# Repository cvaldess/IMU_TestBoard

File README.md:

# IMU Test Board

Four inertial sensors on one small, rigid PCB: **TDK ICM-45686**, **ST LSM6DSV320X**, **ST ASM330LHH** and
**ADI ADXL375**. Because they sit side by side on the same board, all four feel the same shocks, vibration and
temperature on a motocross bike, so their data can be compared directly.

The board is a test fixture for AI MotoLogger, a data logger for a motocross bike. The test results decide which IMU
goes on the main logger board.

*Concept illustration. The renders below show the actual board.*

| Bare board | Assembled board (3D render) |
|:---:|:---:|
|  |  |

## Sensors

| Ref | Part | Type | Accelerometer | Gyroscope | Package |
|---|---|---|---|---|---|
| U2 | TDK InvenSense ICM-45686 | 6-axis IMU | ±32 g | ±4000 dps | LGA-14, 2.5 × 3 mm |
| U3 | ST LSM6DSV320X | 6-axis IMU with a high-g channel | ±16 g, plus a ±320 g channel | ±4000 dps | LGA-14L, 2.5 × 3 mm |
| U4 | ST ASM330LHH | 6-axis IMU, automotive (AEC-Q100, −40 to +105 °C) | ±16 g | ±4000 dps | LGA-14L, 2.5 × 3 mm |
| U5 | ADI ADXL375 | 3-axis accelerometer | ±200 g | — | LGA-14, 3 × 5 mm |

The silkscreen numbers the chip selects and interrupts as `1 ICM · 2 DSV · 3 ASM · 4 ADXL`. The sensors are rotated
on the PCB so that their X, Y and Z axes match (U5 sits at −90° for this reason). The silkscreen marks the axes:
+X to the right, +Y up, and +Z out of the board (the silkscreen says *"+Z hacia fuera"*).

## What it is for

Each test answers one question.

On the bench:

1. Do all four sensors respond? Read `WHO_AM_I` / `DEVID`, and check that the ADXL375 is genuine (see the firmware notes).
2. How noisy is each sensor at rest compared with its datasheet (noise density, offset, drift with temperature)?
3. Do the high-g ranges agree? Under rubber-mallet hits, the ICM-45686 (±32 g) cross-checks the LSM6DSV320X high-g
   channel between 16 and 32 g, and the ADXL375 (±200 g) covers everything above.

On the bike:

4. How high are the real peaks? Do they go past 16 g, or past 32 g? Does any sensor saturate?
5. How does each sensor respond to engine vibration? Compare the spectra and the gyro drift under vibration (vibration rectification).
6. How hot does the board get? Read the internal temperature sensor of all four parts.
7. How accurate is the timing? Time-stamp each FIFO batch with its interrupt against the MCU counter.

The outcome is one of three choices for the main logger: the LSM6DSV320X alone, the ICM-45686 alone, or one of them
plus the ADXL375.

## Design

[`docs/IMU_TEST_BOARD.svg`](docs/IMU_TEST_BOARD.svg) is an English overview of the schematic. It also has the
firmware notes, the test plan, the wiring to the Nucleo and the layout rules. The notes in the KiCad schematic are in
Spanish.

- **Power:** 5 V comes in on J1, then goes through a 600 Ω ferrite bead (FB1) to a dedicated Torex XC6206 3.3 V LDO
  (U1). The IMUs do not share the MCU's 3.3 V rail. D1 is a power LED. The whole board draws less than 10 mA.
- **Shared SPI bus:** an SN74LVC1G32 OR gate sits in front of each IMU's SDI pin and outputs SDI = MOSI OR CS. While
  an IMU's CS is high, its SDI stays at 1, so traffic meant for another IMU can never look like an I²C start condition.
  The ADXL375 cannot turn off its I²C interface (datasheet Rev. B, Fig. 24), and the ICM-45686 datasheet does not say
  how to. RN1 pulls up every CS line, and R2 (33 Ω) sits in series with MISO.
- **ADXL375 supply:** R3 (0 Ω) links VS_ADXL to +3V3. If VS needs filtering, fit a ferrite bead in place of R3, not a
  resistor, because VS must stay ≥ VDD_IO.
- **Test points:** TP1 = +3V3, TP2 = GND, TP3 = ICM-45686 FSYNC (pin 9), for synchronisation tests later.

### J1 pinout and connection to a NUCLEO-U5A5ZJ-Q

J1 is a 1 × 15 header with 2.54 mm pitch. On the bench, it takes a male header and Dupont wires to the Nucleo. On the
bike, use a second board without the header: solder the cable into the J1 holes and tie it down through the two Ø3 mm
holes next to J1 for strain relief. Every signal goes through the Nucleo's Zio connectors, because the morpho headers
come unfitted.

| J1 | Silkscreen | Net | Nucleo | MCU pin | Function |
|---:|---|---|---|---|---|
| 1 | 5V | +5V_IN | CN8-9 | 5V | Nucleo 5 V output |
| 2, 4, 7 | GND | GND | CN8-11, CN7-8, CN8-13 | GND | |
| 3 | SCK | SCK | CN7-10 (D13) | PA5 | SPI1_SCK |
| 5 | MO | MOSI | CN7-14 (D11) | PA7 | SPI1_MOSI |
| 6 | MI | MISO | CN7-12 (D12) | PA6 | SPI1_MISO |
| 8 | CS1 | CS_ICM | CN7-16 (D10) | PD14 | GPIO |
| 9 | CS2 | CS_DSV | CN7-18 (D9) | PD15 | GPIO |
| 10 | CS3 | CS_ASM | CN7-20 (D8) | PF12 | GPIO |
| 11 | CS4 | CS_ADXL | CN10-2 (D7) | PF13 | GPIO |
| 12 | IN1 | INT_ICM | CN10-29 (D32) | PA0 | TIM2_CH1 |
| 13 | IN2 | INT_DSV | CN10-11 (A8) | PA1 | TIM2_CH2 |
| 14 | IN3 | INT_ASM | CN10-32 (D36) | PB10 | TIM2_CH3 |
| 15 | IN4 | INT_ADXL | CN10-34 (D35) | PB11 | TIM2_CH4 |

TIM2 is a 32-bit timer. Each interrupt line goes to one of its input-capture channels, so every FIFO batch gets a
timestamp without interrupt latency.

### Firmware notes

- Use SPI mode 3 for all four sensors (the ADXL375 requires it). The clock limits are 2–5 MHz for the ADXL375 (at
  least 2 MHz for 1600 and 3200 Hz output rates), 10 MHz for the ST parts and 24 MHz for the ICM-45686. At 5 MHz for
  all four, the data takes about 115 KB/s, or ~20 % of the bus.
- At start-up, disable I²C/I3C on U3 (`IF_CFG` 03h, `I2C_I3C_disable` = 1) and on U4 (`CTRL4_C` 13h,
  `I2C_disable` = 1), and turn off the internal pull-up on `AP_SDO` in U2 (ICM-45686 datasheet, Table 10).
- The ADXL375 reports the same `DEVID` (0xE5) as the ADXL345. At rest, a genuine ADXL375 reads 1 g as about 20 LSB
  (49 mg/LSB). A reading of about 256 LSB means the part is a relabelled ADXL345, a real risk with marketplace parts.

## PCB

| | |
|---|---|
| Size | 54.0 × 50.0 mm, rounded corners (r = 1 mm) |
| Layers | 4: top signals + GND pour / In1 GND plane / In2 +3V3 plane / bottom signals + GND pour |
| Thickness | 1.6 mm FR-4, 1 oz outer and 0.5 oz inner copper, no impedance control |
| Tracks | 0.20 mm signals, 0.40 mm power (0.15 mm minimum inside the IMU courtyards) |
| Clearance | 0.15 mm minimum (the LGA pads themselves are 0.15 mm apart) |
| Vias | 0.6 mm pad / 0.3 mm drill, tented |
| Holes | 4 × M3 (3.2 mm NPTH) for mounting, 2 × 3.0 mm NPTH for the cable tie |
| Finish | ENIG preferred: the 0.5 mm pitch LGA packages need flat pads |
| Parts | 32 SMD parts, all on the top side; J1 is through-hole |

The layout follows ST's TN0018 (handling, mounting and soldering of MEMS devices):

- No tracks, vias or copper pour under any IMU on the top layer, and pour keep-out areas under them on all four layers.
- The four IMUs sit in a row in the middle of the board, more than 8 mm from every mounting hole.
- J1 is more than 20 mm from the IMUs, because the cable pulls there. The LDO is more than 9 mm away, because it heats.
- The footprint pads are 0.1 mm larger than the LGA pads, and the solder mask opening is 0.1 mm larger than the pad.
- The paste apertures of U2–U5 are reduced by 0.025 mm per side, to 79 % of the pad area on the 2.5 × 3 mm parts and
  87 % on the ADXL375 (TN0018 §3.3 asks for 70–90 %).

## Fabrication files

| Folder | Contents |
|---|---|
| [`fabrication/pcbway/`](fabrication/pcbway) | The set sent to PCBWay: Gerber zip (RS-274X X2, Excellon drill with PTH and NPTH separate, job file), the same files unzipped plus PDF drill maps, a BOM with manufacturer part numbers, a centroid file, and [`README_PCBWay.txt`](fabrication/pcbway/README_PCBWay.txt) with the full spec and the MEMS handling notes. |
| [`fabrication/jlcpcb/`](fabrication/jlcpcb) | Gerber zip and unzipped files, a BOM with LCSC part numbers where they exist, and the KiCad pick-and-place file. These Gerbers were exported before the PCBWay logo was added. Only the top silkscreen differs; copper, mask, paste and drill are identical. |

The stencil is top side only, 0.12 mm stainless steel. The board is meant to be assembled by hand with the stencil.
When assembling:

- U5 (ADXL375) is rotated 270° on purpose, to align its axes with the other three sensors.
- J1 (1 × 15 header) is fitted by hand, and only on the bench board. TP1–TP3 are bare pads.
- Handle the MEMS parts as TN0018 says (the advice applies to the TDK and ADI parts too):
  - No ultrasonic cleaning.
  - No mechanical shocks: do not drop the parts or the boards.
  - Reflow to IPC/JEDEC J-STD-020, cooling no faster than 3 °C/s.
  - No solder on the sides of the LGA packages.
  - No underfill and no conformal coating.

## Opening the project

You need KiCad 10. Open [`kicad/prueba_imu.kicad_pro`](kicad/prueba_imu.kicad_pro) (*prueba_imu* is Spanish for
"IMU test").

- The symbols for the four IMUs are in [`kicad/libs/ai_motologger.kicad_sym`](kicad/libs/ai_motologger.kicad_sym),
  registered in the project's `sym-lib-table`.
- Footprints and 3D models come from the standard KiCad 10 libraries. The PCBWay logo is embedded in the board file.
- [`kicad/prueba_imu.kicad_dru`](kicad/prueba_imu.kicad_dru) adds three custom design rules (its comments are in
  Spanish):
  - `imu_pistas_finas` lets tracks narrow to 0.15–0.2 mm inside the IMU courtyards, so that power nets can reach the
    LGA pads.
  - `pasta_imu` applies the −0.025 mm solder paste margin on U2–U5. Only the absolute paste margin reaches the Gerber
    output; the relative margin does not.
  - `termico_un_radio` accepts a single thermal spoke on small SMD pads.

## Repository layout

```
kicad/          KiCad 10 project: schematic, PCB, custom DRC rules and the IMU symbol library
fabrication/    Gerber, drill, BOM and placement files (PCBWay and JLCPCB sets)
docs/           English schematic overview (SVG and PNG)
images/         Renders and the cover illustration
```

## Status

Rev 0.1. PCBWay sponsored the PCBs and the stencil (November 2026). The board has not been assembled or tested yet,
so treat the design as unverified. The next steps are hand assembly with the stencil, bench tests on a
NUCLEO-U5A5ZJ-Q, and then rides on a Yamaha YZ 125 test bike.

## Acknowledgements

Thanks to [PCBWay](https://www.pcbway.com) for sponsoring the PCBs and the stencil for this board.

## License

Copyright CValdesS 2026.

This source describes Open Hardware and is licensed under the CERN-OHL-S v2.

You may redistribute and modify this source and make products using it under the terms of the
[CERN-OHL-S v2](https://ohwr.org/cern_ohl_s_v2.txt). The full text is in [`LICENSE`](LICENSE).

This source is distributed WITHOUT ANY EXPRESS OR IMPLIED WARRANTY, INCLUDING OF MERCHANTABILITY, SATISFACTORY QUALITY
AND FITNESS FOR A PARTICULAR PURPOSE. Please see the CERN-OHL-S v2 for applicable conditions.

Source location: <https://github.com/cvaldess/IMU_TestBoard>

As per CERN-OHL-S v2 section 4, should You produce hardware based on this source, You must where practicable maintain
the Source Location visible on the external case of the Gizmo or other products you make using this source.

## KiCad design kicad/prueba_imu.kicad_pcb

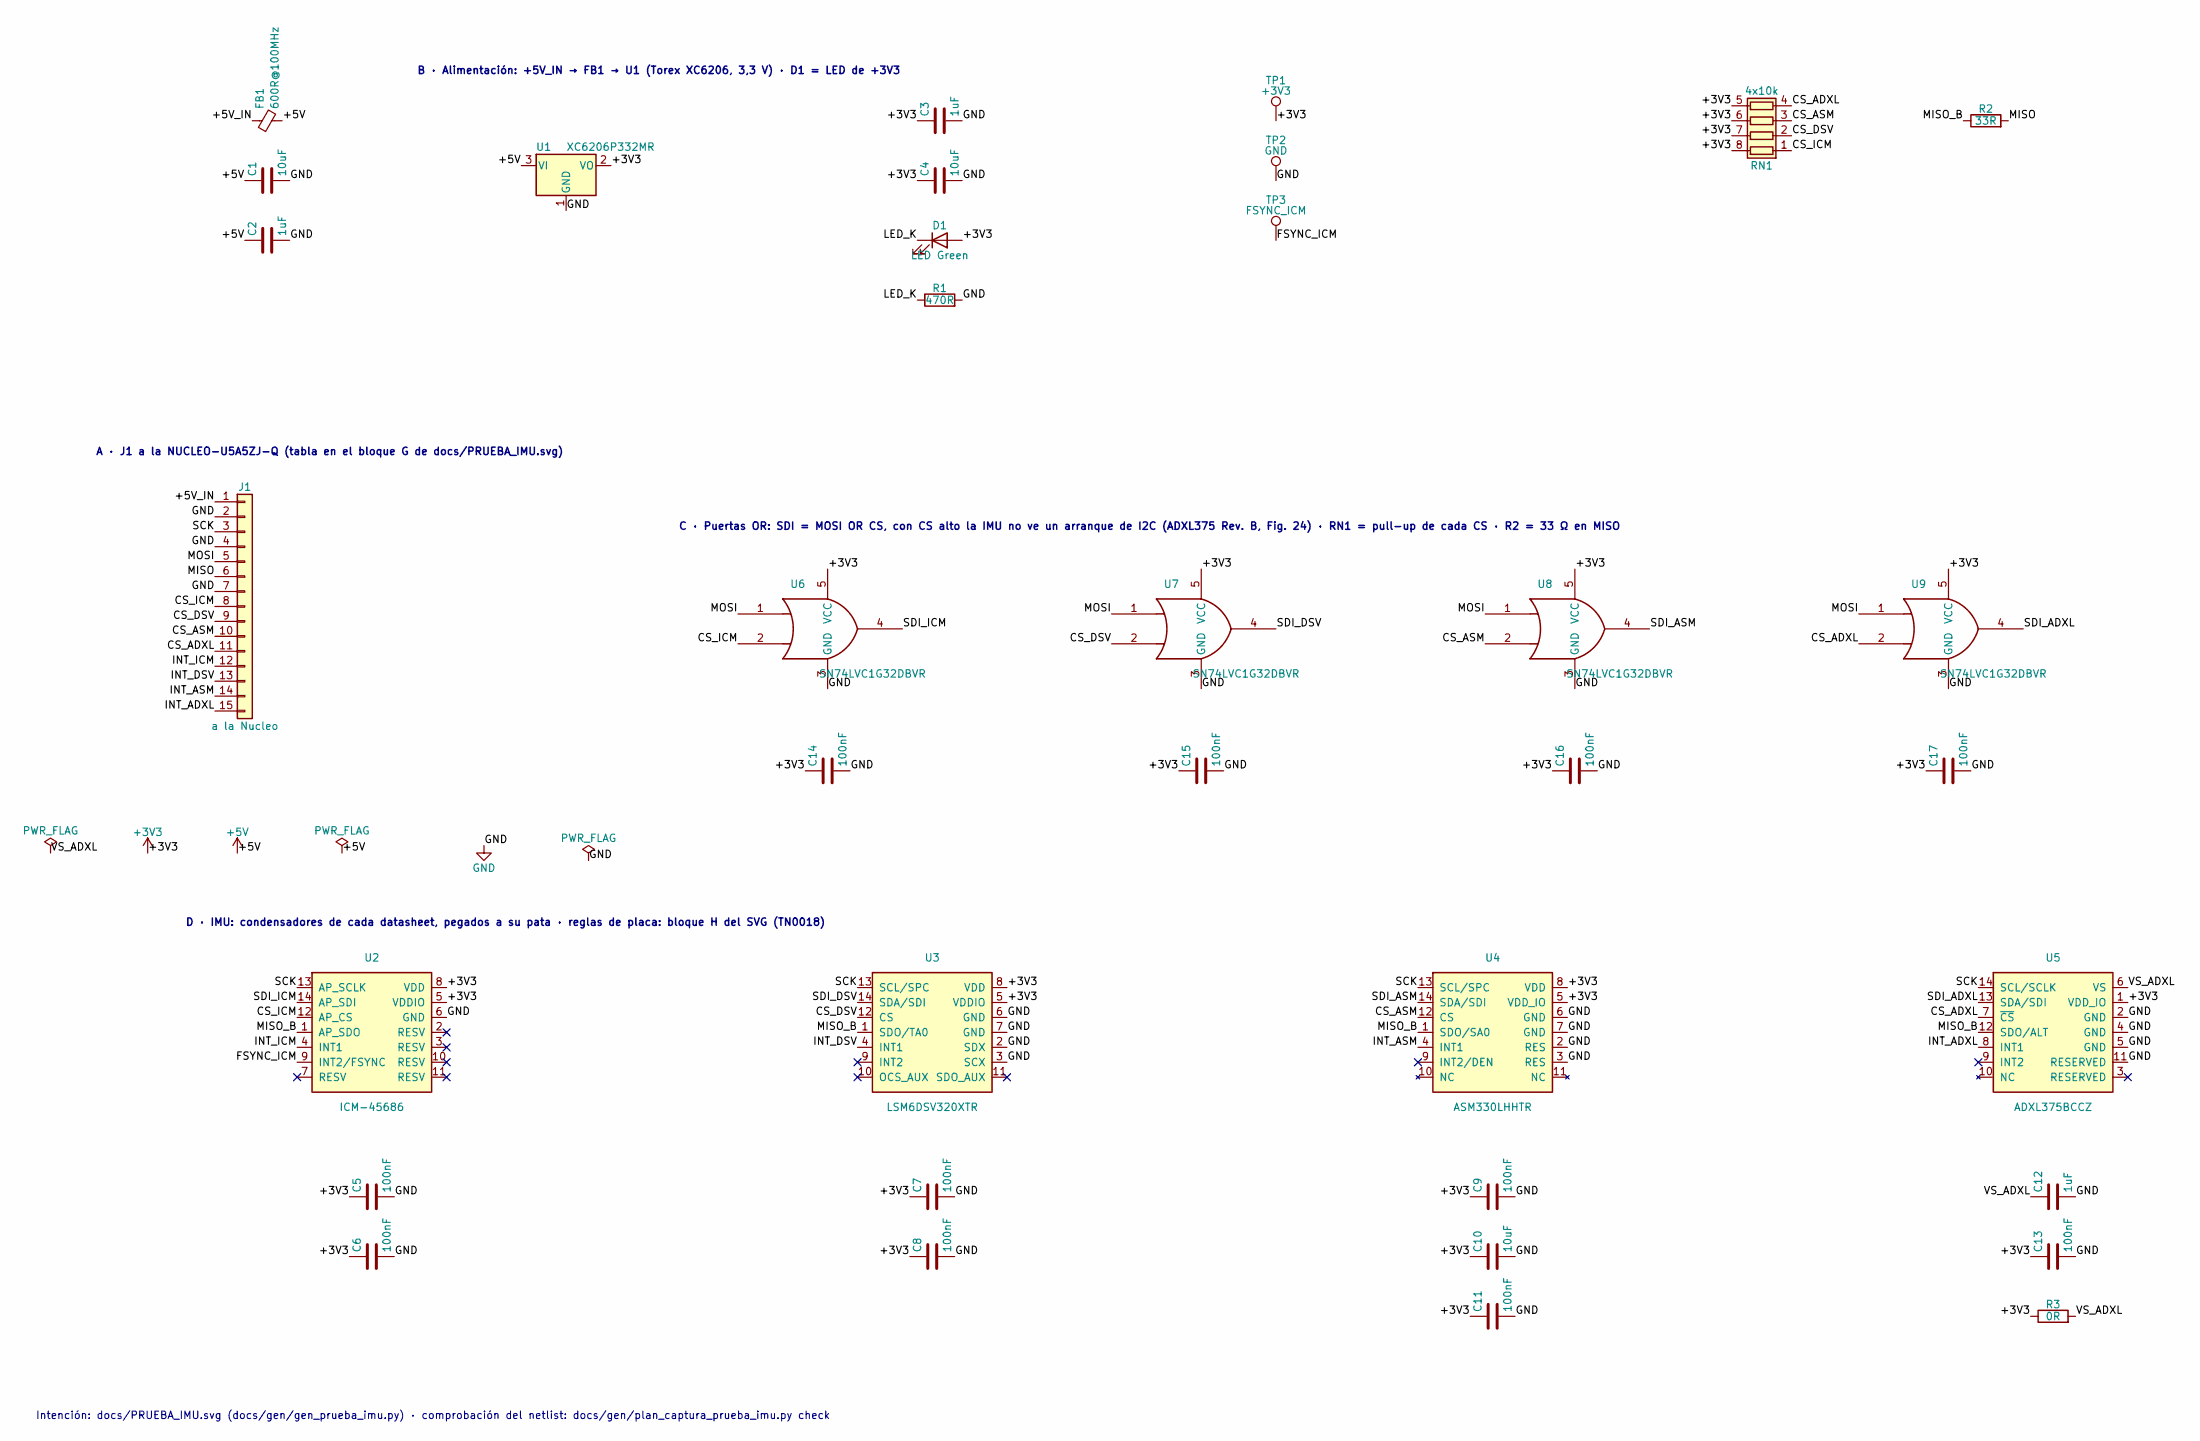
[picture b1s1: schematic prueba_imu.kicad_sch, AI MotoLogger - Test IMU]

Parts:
C1, C4, C10: 10uF; C_0603_1608Metric
C2, C3, C12: 1uF; C_0603_1608Metric
C5, C6, C7, C8, C9, C11, C13, C14, C15, C16, C17: 100nF; C_0603_1608Metric
D1: LED Green; LED_0603_1608Metric
FB1: 600R@100MHz; L_0603_1608Metric; MPN CBW160808U601T; LCSC Part C139183
J1: a la Nucleo; PinHeader_1x15_P2.54mm_Vertical
R1: 470R; R_0603_1608Metric
R2: 33R; R_0603_1608Metric
R3: 0R; R_0603_1608Metric
RN1: 4x10k; R_Array_Convex_4x0603; MPN YC164-FR-0710KL; LCSC Part C110924
TP1: +3V3; TestPoint_Pad_D1.5mm
TP2: GND; TestPoint_Pad_D1.5mm
TP3: FSYNC_ICM; TestPoint_Pad_D1.5mm
U1: XC6206P332MR; SOT-23-3; MPN XC6206P332MR; LCSC Part C5446
U2: ICM-45686; LGA-14_3x2.5mm_P0.5mm_LayoutBorder3x4y; MPN ICM-45686; LCSC Part C22459454
U3: LSM6DSV320XTR; LGA-14_3x2.5mm_P0.5mm_LayoutBorder3x4y; MPN LSM6DSV320XTR; LCSC Part C26633007
U4: ASM330LHHTR; LGA-14_3x2.5mm_P0.5mm_LayoutBorder3x4y; MPN ASM330LHHTR; LCSC Part C459826
U5: ADXL375BCCZ; LGA-14_3x5mm_P0.8mm_LayoutBorder1x6y; MPN ADXL375BCCZ
U6, U7, U8, U9: SN74LVC1G32DBVR; SOT-23-5; MPN SN74LVC1G32DBVR; LCSC Part C10096

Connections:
+3V3: C3.1, C4.1, C5.1, C6.1, C7.1, C8.1, C9.1, C10.1, C11.1, C13.1, C14.1, C15.1, C16.1, C17.1, D1.2 (A), R3.1, RN1.5 (R4.2), RN1.6 (R3.2), RN1.7 (R2.2), RN1.8 (R1.2), TP1.1 (1_1), U1.2 (VO), U2.5 (VDDIO), U2.8 (VDD), U3.5 (VDDIO), U3.8 (VDD), U4.5 (VDD_IO), U4.8 (VDD), U5.1 (VDD_IO), U6.5 (VCC), U7.5 (VCC), U8.5 (VCC), U9.5 (VCC)
+5V: C1.1, C2.1, FB1.2, U1.3 (VI)
/+5V_IN: FB1.1, J1.1
/CS_ADXL: J1.11, RN1.4 (R4.1), U5.7 (~CS), U9.2
/CS_ASM: J1.10, RN1.3 (R3.1), U4.12 (CS), U8.2
/CS_DSV: J1.9, RN1.2 (R2.1), U3.12 (CS), U7.2
/CS_ICM: J1.8, RN1.1 (R1.1), U2.12 (AP_CS), U6.2
/FSYNC_ICM: TP3.1 (1_1), U2.9 (INT2/FSYNC)
/INT_ADXL: J1.15, U5.8 (INT1)
/INT_ASM: J1.14, U4.4 (INT1)
/INT_DSV: J1.13, U3.4 (INT1)
/INT_ICM: J1.12, U2.4 (INT1)
/LED_K: D1.1 (K), R1.1
/MISO: J1.6, R2.2
/MISO_B: R2.1, U2.1 (AP_SDO), U3.1 (SDO/TA0), U4.1 (SDO/SA0), U5.12 (SDO/ALT)
/MOSI: J1.5, U6.1, U7.1, U8.1, U9.1
/SCK: J1.3, U2.13 (AP_SCLK), U3.13 (SCL/SPC), U4.13 (SCL/SPC), U5.14 (SCL/SCLK)
/SDI_ADXL: U5.13 (SDA/SDI), U9.4
/SDI_ASM: U4.14 (SDA/SDI), U8.4
/SDI_DSV: U3.14 (SDA/SDI), U7.4
/SDI_ICM: U2.14 (AP_SDI), U6.4
/VS_ADXL: C12.1, R3.2, U5.6 (VS)
GND: C1.2, C2.2, C3.2, C4.2, C5.2, C6.2, C7.2, C8.2, C9.2, C10.2, C11.2, C12.2, C13.2, C14.2, C15.2, C16.2, C17.2, J1.2, J1.4, J1.7, R1.2, TP2.1 (1_1), U1.1 (GND), U2.6 (GND), U3.2 (SDX), U3.3 (SCX), U3.6 (GND), U3.7 (GND), U4.2 (RES), U4.3 (RES), U4.6 (GND), U4.7 (GND), U5.2 (GND), U5.4 (GND), U5.5 (GND), U5.11 (RESERVED), U6.3 (GND), U7.3 (GND), U8.3 (GND), U9.3 (GND)

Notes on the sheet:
Intención: docs/PRUEBA_IMU.svg (docs/gen/gen_prueba_imu.py) · comprobación del netlist: docs/gen/plan_captura_prueba_imu.py check
B · Alimentación: +5V_IN → FB1 → U1 (Torex XC6206, 3,3 V) · D1 = LED de +3V3
A · J1 a la NUCLEO-U5A5ZJ-Q (tabla en el bloque G de docs/PRUEBA_IMU.svg)
C · Puertas OR: SDI = MOSI OR CS, con CS alto la IMU no ve un arranque de I2C (ADXL375 Rev. B, Fig. 24) · RN1 = pull-up de cada CS · R2 = 33 Ω en MISO
D · IMU: condensadores de cada datasheet, pegados a su pata · reglas de placa: bloque H del SVG (TN0018)

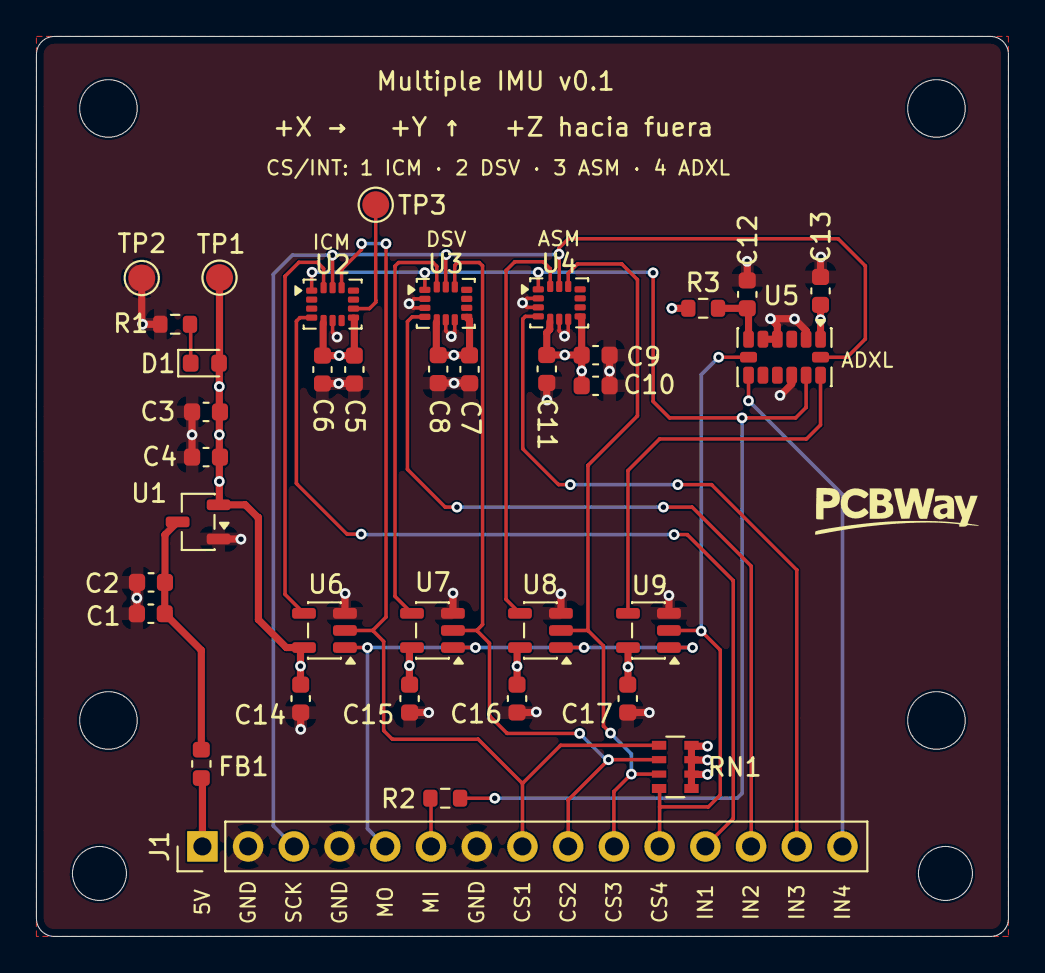
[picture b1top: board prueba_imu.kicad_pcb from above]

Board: 4 copper layers, 54.0 x 50.0 mm, 42 parts (0 on the bottom side), 23 nets.

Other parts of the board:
H1, H2, H3, H4: MountingHole_3.2mm_M3
H5, H6: MountingHole_3mm

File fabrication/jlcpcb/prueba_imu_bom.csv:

"Reference","Value","Footprint","Qty","DNP","LCSC Part","MPN","Manufacturer"
"U2","ICM-45686","LGA-14 2.5x3","1","","C22459454","ICM-45686","TDK InvenSense"
"U3","LSM6DSV320XTR","LGA-14L 2.5x3","1","","C26633007","LSM6DSV320XTR","STMicroelectronics"
"U4","ASM330LHHTR","LGA-14L 2.5x3","1","","C459826","ASM330LHHTR","STMicroelectronics"
"U5","ADXL375BCCZ","LGA-14 3x5","1","","","ADXL375BCCZ","Analog Devices"
"U6,U7,U8,U9","SN74LVC1G32DBVR","SOT-23-5","4","","C10096","SN74LVC1G32DBVR","TI"
"U1","XC6206P332MR","SOT-23","1","","C5446","XC6206P332MR","TOREX"
"FB1","CBW160808U601T","0603","1","","C139183","CBW160808U601T","FH"
"RN1","YC164-FR-0710KL","4x0603","1","","C110924","YC164-FR-0710KL","YAGEO"
"C5,C6,C7,C8,C9,C11,C13,C14,C15,C16,C17","100nF","0603","11","","","",""
"C2,C3,C12","1uF","0603","3","","","",""
"C1,C4,C10","10uF","0603","3","","","",""
"R1","470R","0603","1","","","",""
"R2","33R","0603","1","","","",""
"R3","0R","0603","1","","","",""
"D1","LED Green","0603","1","","","",""
